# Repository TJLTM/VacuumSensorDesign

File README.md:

# VacuumSensorDesign
A Vacuum Sesnor Design for Automotive applications
I'm too lazy to really write too much here. Basically in my search for telemtry from older cars for tuning and diagnostic purposes, I needed a manifold Vacuum Sensor that can be connected to SBC/MCU. Looking in the marketplace for equiv sensors there are few. and even looking in catalogs for raw sensors for this application there wasn't much in the way of vacuum sensors. the only equiv i found was the https://www.glowshiftdirect.com/vacuum-gauges/ looking at this one after i spent months searching for something i could build myself. shows that i basically picked the same sensor but from honeywell instead of NXP. Plus side for the honeywell sensor is that it doesn't require special housing and mechaincal design to mount the board and have a good seal to the sensor so it can go into a generic enclosure. 

Basic specs
1. Read a vacuum signal from +/- 30psi (+/- 206KPa)
2. Output an protected MCU ADC value (0-4.5v ~2.5v for zero reading ie at atmospheric pressure)  
5. With some Re-calibration and tweaks this design should work for 3.3 ADC inputs 
6. Run on car voltages (12 volt neg ground) 
7. ability to be re-caled in the field if need be

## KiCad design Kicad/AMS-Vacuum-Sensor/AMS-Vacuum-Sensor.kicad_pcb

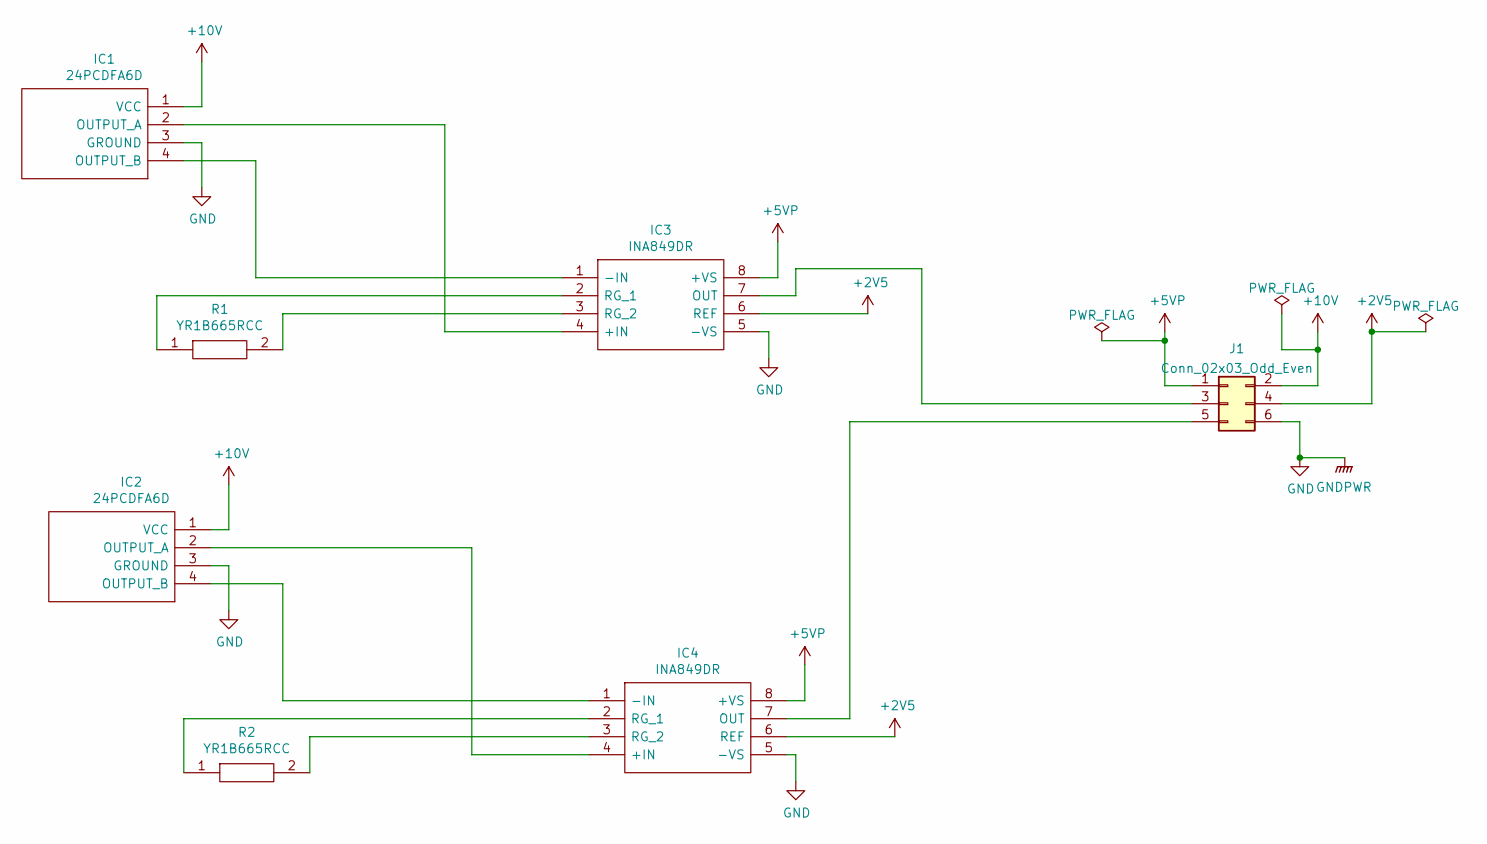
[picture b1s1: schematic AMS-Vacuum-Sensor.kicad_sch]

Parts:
IC1, IC2: 24PCDFA6D; Mouser Part Number 785-24PCDFA6D
IC3, IC4: INA849DR; SOIC127P600X175-8N; Mouser Part Number 595-INA849DR
J1: Conn_02x03_Odd_Even; PinHeader_2x03_P2.54mm_Vertical
R1, R2: YR1B665RCC; RESAD1550W60L630D230; Mouser Part Number 279-YR1B665RCC

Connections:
+2V5: IC3.6 (REF), IC4.6 (REF), J1.4
+5VP: IC3.8 (+VS), IC4.8 (+VS), J1.1
+10V: IC1.1 (VCC), IC2.1 (VCC), J1.2
GND: IC1.3 (GROUND), IC2.3 (GROUND), IC3.5 (-VS), IC4.5 (-VS), J1.6
unnamed: IC1.2 (OUTPUT_A), IC3.4 (+IN)
unnamed: IC1.4 (OUTPUT_B), IC3.1 (-IN)
unnamed: IC2.2 (OUTPUT_A), IC4.4 (+IN)
unnamed: IC2.4 (OUTPUT_B), IC4.1 (-IN)
unnamed: IC3.2 (RG_1), R1.1
unnamed: IC3.3 (RG_2), R1.2
unnamed: IC3.7 (OUT), J1.3
unnamed: IC4.2 (RG_1), R2.1
unnamed: IC4.3 (RG_2), R2.2
unnamed: IC4.7 (OUT), J1.5

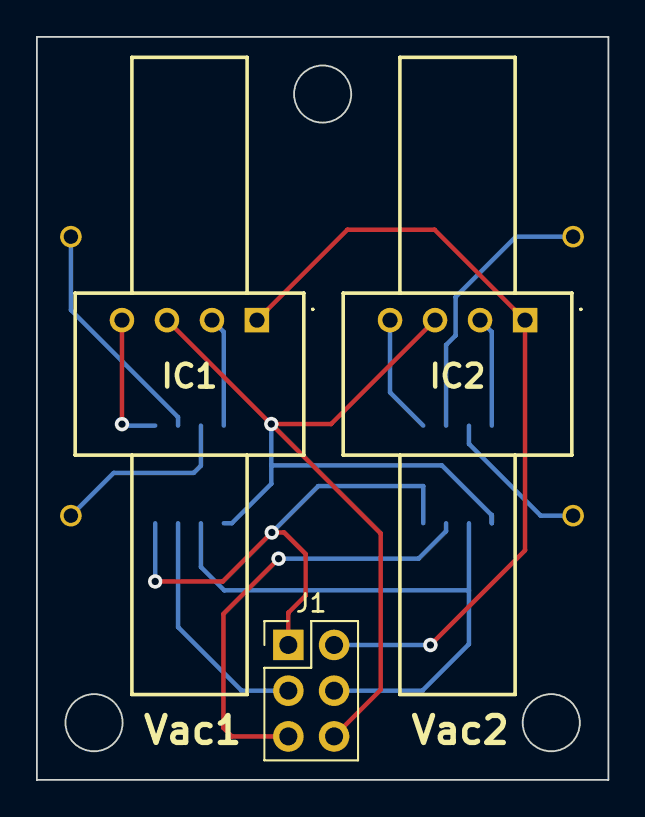
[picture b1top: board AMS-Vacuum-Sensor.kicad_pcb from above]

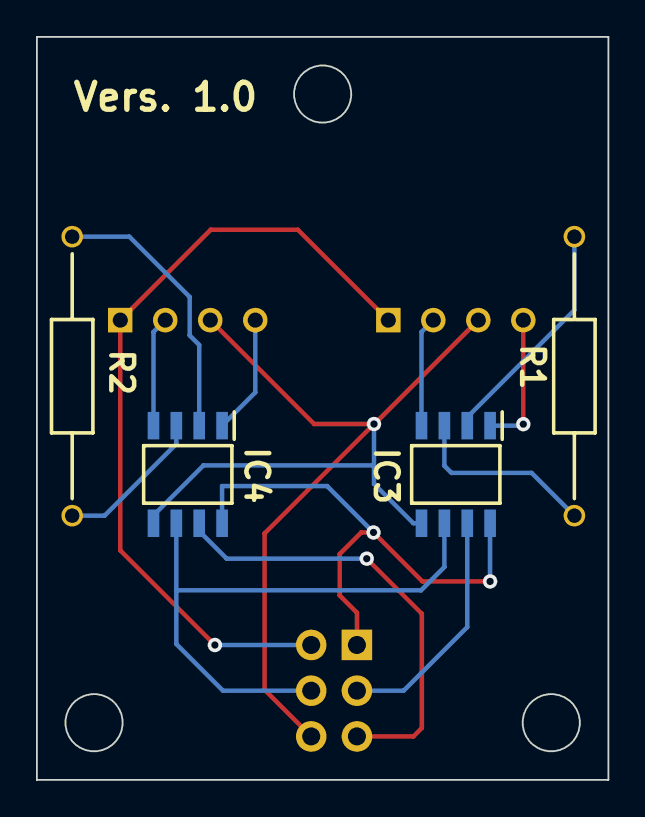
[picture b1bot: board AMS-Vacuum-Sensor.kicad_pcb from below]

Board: 2 copper layers, 31.8 x 41.3 mm, 7 parts (4 on the bottom side), 14 nets.

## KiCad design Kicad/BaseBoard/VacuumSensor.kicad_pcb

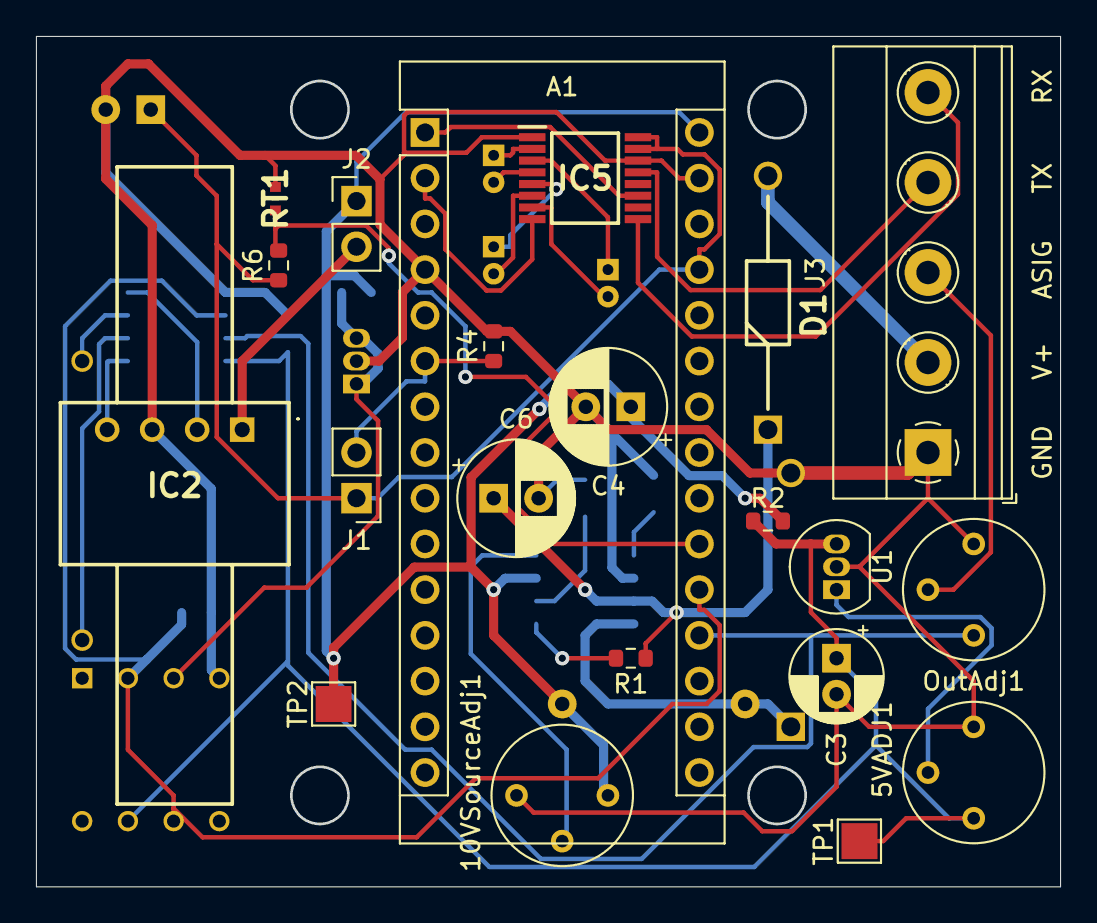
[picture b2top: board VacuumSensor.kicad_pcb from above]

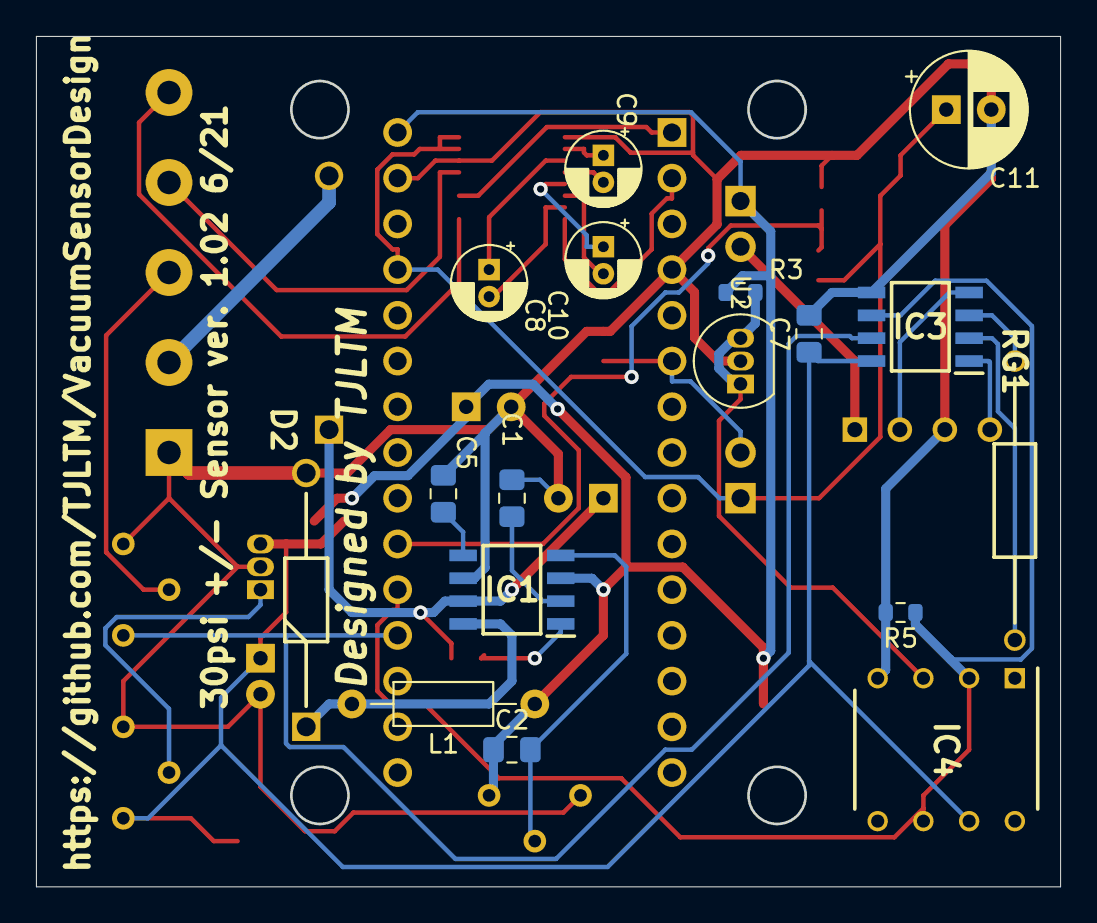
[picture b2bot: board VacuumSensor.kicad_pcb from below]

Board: 2 copper layers, 56.9 x 47.2 mm, 38 parts (17 on the bottom side), 33 nets.

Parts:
5VADJ1: 20k; Potentiometer_Bourns_3339P_Vertical
10VSourceAdj1: 10k; Potentiometer_Bourns_3339P_Vertical
A1: Arduino_Nano_v3.x; Arduino_Nano
C1, C5: 0.1uF; C_0805_2012Metric_Pad1.15x1.40mm_HandSolder
C2: 33nF; C_0805_2012Metric_Pad1.15x1.40mm_HandSolder
C3: 1uF; CP_Radial_D5.0mm_P2.00mm
C4: 120uf; CP_Radial_D6.3mm_P2.50mm
C6: 68uF; CP_Radial_D6.3mm_P2.50mm
C7: 100nF; C_0805_2012Metric_Pad1.15x1.40mm_HandSolder
C8, C9, C10: 0.22uF; CP_Radial_D4.0mm_P1.50mm
C11: 0.1uF; CP_Radial_D6.3mm_P2.50mm
D1, D2: 1N5817; DIOAD1414W86L464D238
IC1: LM2597MX-ADJ_NOPB; SOIC127P600X175-8N
IC2: 24PCDFA6D
IC3: INA849DR; SOIC127P600X175-8N
IC4: TL071CP; DIP794W53P254L959H508Q8N
IC5: SP3220EBEY-L_TR; SOP65P640X120-16N
J1, J2: Conn_01x02; PinHeader_1x02_P2.54mm_Vertical
J3: Screw_Terminal_01x05; TerminalBlock_Phoenix_MKDS-1,5-5_1x05_P5.00mm_Horizontal
L1: L; L_Axial_L5.3mm_D2.2mm_P10.16mm_Horizontal_Vishay_IM-1
OutAdj1: 1M; Potentiometer_Bourns_3339P_Vertical
R1, R6: 10k; R_0603_1608Metric
R2, R3: 1k; R_0603_1608Metric
R4: 20k; R_0603_1608Metric
R5: 10M; R_0603_1608Metric
RG1: YR1B665RCC; RESAD1550W60L630D230
RT1: NTCSP103JF103FT1S; THRMC1005X55N
TP1, TP2: TestPoint; TestPoint_Pad_2.0x2.0mm
U1, U2: TL431LP; TO-92_Inline

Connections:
+5V: 5VADJ1.1, C3.1, C7.1, IC3.8, IC4.7, R2.2, TP1.1, U1.3
+10V: 10VSourceAdj1.1, A1.30, C2.1, C4.1, IC1.3, J2.1, L1.1, R2.1, R3.1, TP2.1
+VDC: C6.1, D1.1, IC1.7, R1.1
GND: 5VADJ1.3, 10VSourceAdj1.3, A1.4, A1.29, C1.2, C3.2, C4.2, C5.2, C6.2, C7.2, C11.2, D2.2, IC1.6, IC2.3, IC3.5, IC4.4, IC5.1, IC5.14, J3.1, OutAdj1.3, R4.2, R5.2, RT1.2, U1.2, U2.2
unnamed: 5VADJ1.2, U1.1
unnamed: 10VSourceAdj1.2, C2.2, IC1.4
unnamed: A1.1, IC5.11
unnamed: A1.2, IC5.8
unnamed: A1.6, J1.2, R4.1
unnamed: A1.19, IC3.7, OutAdj1.1
unnamed: A1.20, IC3.6, IC4.2, IC4.6, R5.1
unnamed: A1.21, R6.2, RT1.1
unnamed: A1.27, C11.1, IC5.15, IC5.16, J1.1, R6.1
unnamed: C1.1, IC1.2
unnamed: C5.1, IC1.5
unnamed: C8.1, IC5.3
unnamed: C8.2, IC5.7
unnamed: C9.1, IC5.2
unnamed: C9.2, IC5.4
unnamed: C10.1, IC5.5
unnamed: C10.2, IC5.6
unnamed: D1.2, J3.2
unnamed: D2.1, IC1.8, L1.2
unnamed: IC1.1, R1.2
unnamed: IC2.1, J2.2
unnamed: IC2.2, IC3.4
unnamed: IC2.4, IC3.1
unnamed: IC3.2, RG1.2
unnamed: IC3.3, RG1.1
unnamed: IC4.3, R3.2, U2.1, U2.3
unnamed: IC5.9, J3.5
unnamed: IC5.13, J3.4
unnamed: J3.3, OutAdj1.2

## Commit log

2021-04-17 Update README.md
    added what the basic what the hell i'm doing.
2021-05-16 pushing up my current design and fab files. Code and Docs to follow.
2021-05-16 Initial Code for Arduino. needs to be re verified for calibration.
2021-05-16 Update README.md
    making some corrections and updates.
2021-05-16 adding cad files for a spacer that goes under Honeywell 24PCDFA6D when mounting onto the PCB
2021-05-26 1.02 update removed the unity gain output op amp and Gain trim pot and replaced it witha 0.1% 665 ohm resistor for the instrumentation amp. simplified the voltage reference and 5v circuits. Added an 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
2021-05-26 adding the Fab Files for 1.02
2022-01-15 upgrade to 6.0 kicad
2022-01-15 keeping the original single board design and adding a second one with a new base board that will use the same dual sensor board as the AMS
2022-01-15 adding the AMS vac sensor board design here.
2022-02-18 adding the new fab files for AMS board
2022-02-18 removing old fab files for other design
2022-02-20 cleaning up the sensor designs because they where a mess and i'm going to make two different ones one that is a single board and one that is a carrier for the AMS dual version
2022-02-20 initial for AMS base Carrier
2022-02-20 don't know why git is having an issue with this file.
2023-07-14 updating all the kicad files to 7.0
2023-08-22 * removing the other designs * fixing up the original design
2023-08-22 rename
2023-08-22 moving and reorganizing
